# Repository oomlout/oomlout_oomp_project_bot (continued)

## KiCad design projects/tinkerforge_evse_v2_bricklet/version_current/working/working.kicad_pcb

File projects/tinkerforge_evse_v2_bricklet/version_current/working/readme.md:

# evse-v2-bricklet by Tinkerforge  
This is a harvested standardized copy of a project from github.  
The original project can be found at:  
https://github.com/Tinkerforge/evse-v2-bricklet  
Please consult that link for additional, details, files, and license information.  
Note: It was auto harvested and if the original repo had more than one board file or anything out of the ordinary the files here are likely not representative.

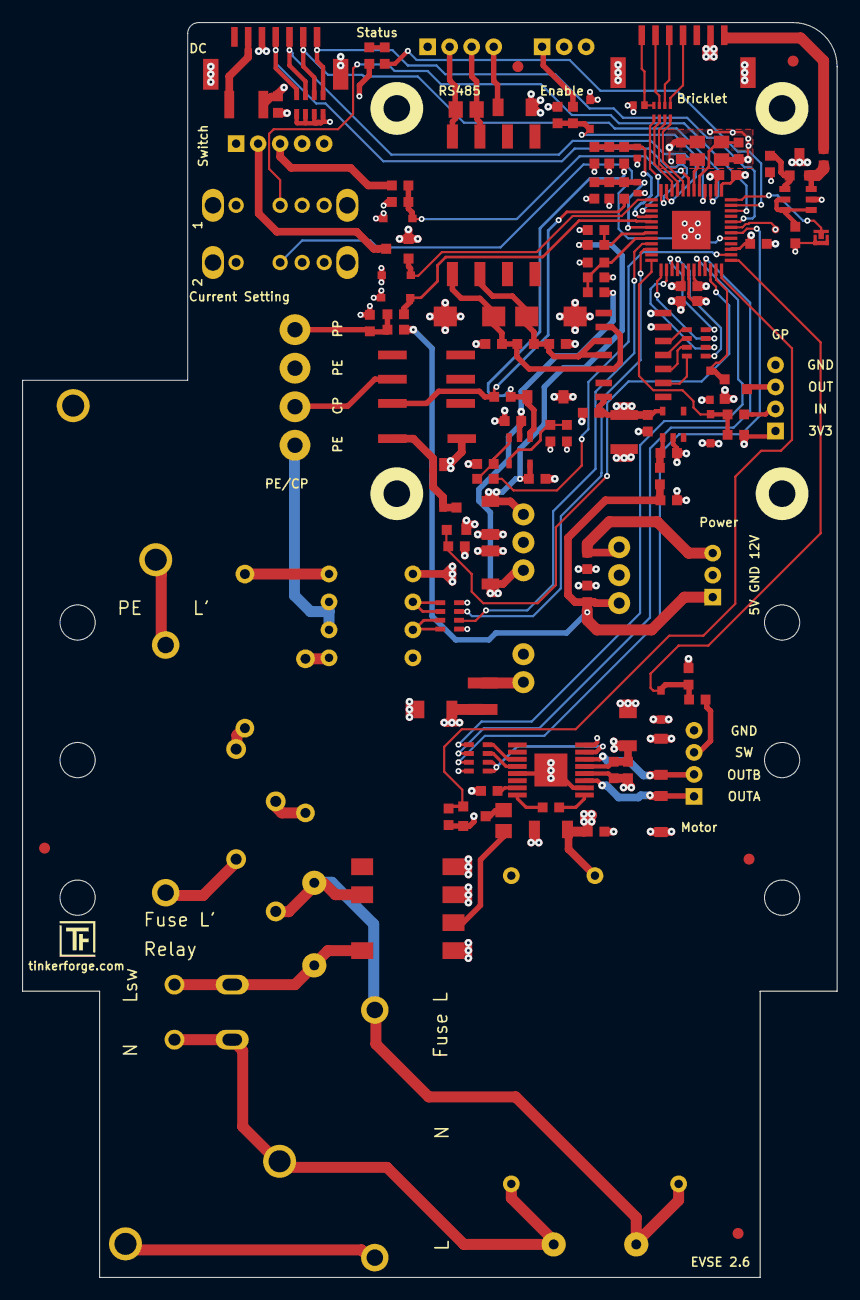
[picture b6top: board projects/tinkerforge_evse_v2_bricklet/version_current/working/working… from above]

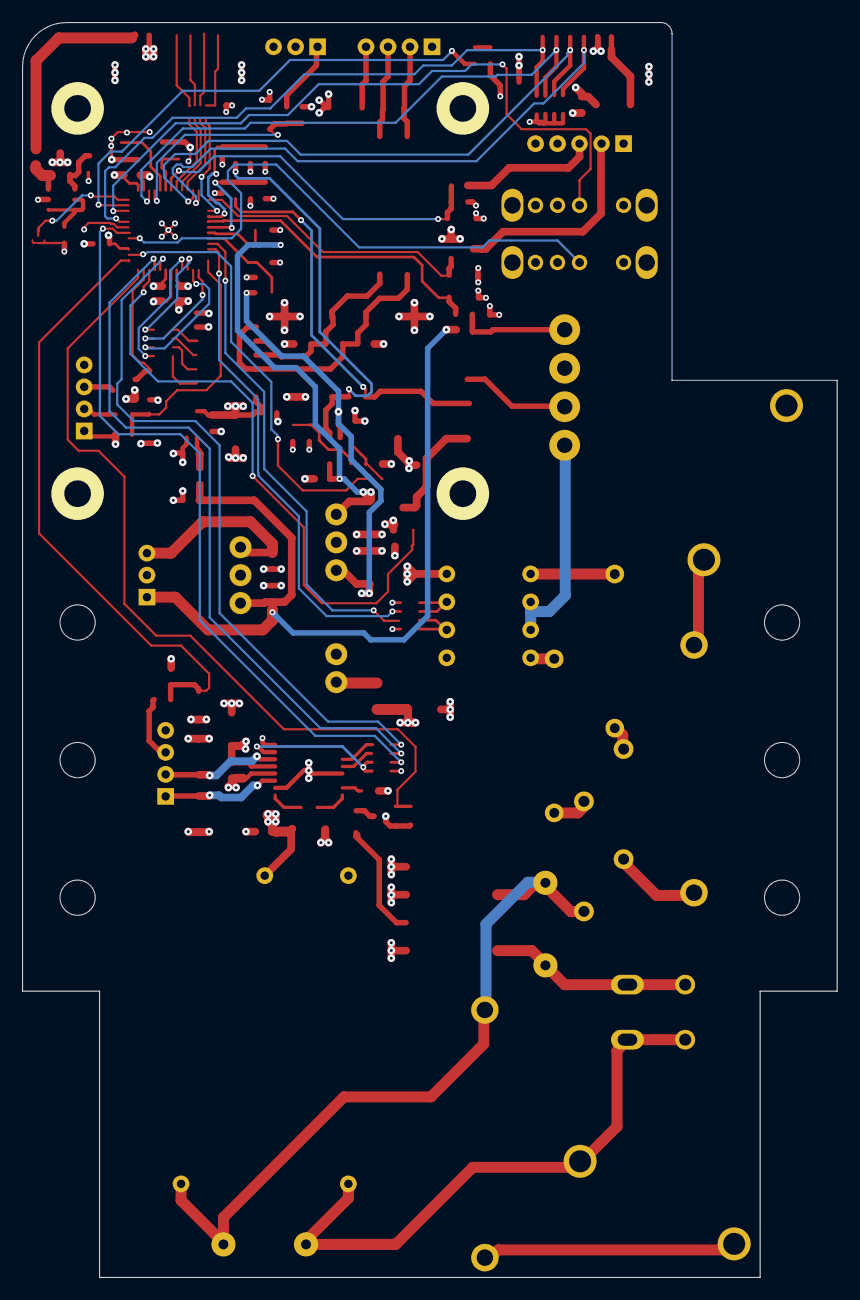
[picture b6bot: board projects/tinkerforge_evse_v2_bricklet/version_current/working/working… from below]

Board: 4 copper layers, 74.0 x 114.0 mm, 144 parts (2 on the bottom side), 100 nets.

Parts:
A101, A102, A103, A104: DRILL; DRILL_NP_35
A105, A106: Rail; din-rail-mount
C101: 220pF; C0402F
C102, C127, C130, C132: 100nF; C0603F
C103, C106, C107, C124, C125, C126: 1uF; C0603F
C104, C105, C108, C109: 4.7uF/50V; C1206
C110: 2.2uF; C0603F
C111: 100uF; C1210
C112, C113, C116, C117, C118, C119: 100nF/30V; C0603F
C114: 10uF; C1206
C120, C121: DNP; C0402F
C128, C129: 10pF; C0603F
C131: 220nF; C0603F
D101, D102, D104, D107, D110, D113, D114: ‎PESD3V3L1BA; SOD-323
D103: blue; D0603F
D105, D108, D109: SMF4L13CA; SOD-123FL
D106, D111: SMAJ24CA; DO-214AC
D112: B0520LW-7; SOD-123
D115, D116: 1N4007; DO-41
F101, F102: FUSE; Fuse-Holder-5x20
Fiducial_Mark: VAL**; Fiducial_Mark
Fiducial_Mark#2, Fiducial_Mark#3, Fiducial_Mark#4, Fiducial_Mark#5: VAL**; Fiducial_Mark
J101: Boot; SolderJumper
L101, L103: FB; R0603F
L102: NR3015T6R8M; NR3030
L104: WE-SL
P101: CON-SENSOR2; CON-SENSOR2_180
P102: Relay; LSF-SMT-500-02-135
P103, P104: L'+PE; wm_2491620000
P105: CP/PP/PE; OQ_4P_Vertical
P106: Power; JST-PH-3-THT
P107: Motor; JST-PH-4-THT
P108: Switch_LED; JST-PH-5-THT
P109: Enable; JST-PH-3-THT
P110: MODBUS; JST-PH-4-THT
P111: Debug; DEBUG_PAD
P112: DC-Protect; CON-SENSOR2_180
P113: GP; JST-PH-4-THT
PTC101: PTC 0.45A; C1206
Q101, Q103, Q104: 2N7002P; SOT23GDS
Q102: SI2305CDS-T1-GE3; SOT23GDS
Q105: SSM3J355R,LF; SOT23GDS
R1: 0; R1210
R101: 100; R0603F
R102, R110, R125: 75k; R0603F
R103, R112, R119, R121, R132, R139, R140: 10k; R0603F
R104, R108, R126, R129: 300k; R0603F
R105, R106, R109, R122, R127, R130: 100k; R0603F
R107: 910; R0603F
R111, R115, R117, R120, R123, R124, R131, R138: 1k; R0603F
R113, R128: MOV-10D391KTR; VAR_10mm
R114, R137: 120; R0805E
R116, R118: RNF12FTD249K; RNF12-2
R133: 47k; R0603F
R134, R136: 750; R0603F
R135: DNP; R0603F
R141: 2k; R0603F
REL101: AGQ200S12Z; AGQ2X0
RP101: 82; 4X0402
RP102: 10k; 0603X4
RP103, RP104: 1k; 4X0603
RP105: 10k; 4X0603
SW101, SW102: OS103011MS8QP1
U101: XMC1404; QFN48-EP2
U102: PEM1-S12-D12-S; PEM1S
U103: DMMT5401; SOT26
U105: OPA171AIDBV; SOT23-5
U106: A5950GLP; TSSOP16_EP
U108: AQH3213AX; AQ-H
U109: HCPL2731; DIP-8
U110: TPS70933DBVR; SOT23-5
U111: IRM02-12; IRM02
U112: WPMDL110
U113: SP3491; SOIC-14_3.9x8.7mm_Pitch1.27mm
X101: 16MHz; CRYSTAL_3225

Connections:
3V3: C102.1, C110.1, C111.1, C127.1, C130.1, C131.1, C132.2, D103.1 (A), P113.1, Q102.S, R102.2, R103.2, R105.2, R110.1, R115.2, R119.2, R121.2, R125.1, R132.2, R134.1, R139.2, RP103.5 (R4), RP103.6 (R3), RP103.7 (R2), RP103.8 (R1), RP104.1, RP105.1, RP105.4, SW101.4, SW102.4, U101.18 (VDD), U101.19 (VDDP), U101.27 (VDDP), U101.38 (VDDP), U106.8 (RESETn), U109.8 (VCC), U110.5 (OUT), U113.14 (VCC)
5V: C103.1, C107.1, C126.1, L101.2, P106.1, Q105.D, R1.1, R111.2, U103.5, U112.3 (VOUT)
485-D: RP102.4, U101.15 (P2.12/AIO)
485-DE: RP102.3, U101.13 (P2.10/AIO)
485-R: RP102.1, U101.16 (P2.13/AIO)
485-~REB: RP102.2, U101.14 (P2.11/AIO)
+12V: C109.1, C113.2, R129.2, U102.7 (+Vo), U105.5 (V+)
-12V: C108.2, C112.2, R104.2, U102.5 (-Vo), U105.2 (V-)
AC1: RP105.3, U101.9 (P2.6_AI)
AC2: RP105.2, U101.10 (P2.7_AI)
BOOT: J101.2, U101.36 (P0.7_IO)
CP-DISCONNECT: Q103.G, R138.2, U101.22 (P1.4_IHO)
CP-PWM: R101.2, U101.26 (P1.0_IHO)
CPOUT: R107.2, R108.2, REL101.7
CPOUT2: P105.2, REL101.6
DC-ERR: P112.1, RP103.4, U101.32 (P0.3_IO)
DC-TST: P112.2, RP103.3, U101.39 (P0.8_IO/RTC_XTAL1)
DC-X6: P112.3, RP103.2, U101.47 (P4.4_IO)
DC-X30: P112.4, RP103.1, U101.48 (P4.5_IO)
ENABLE: D102.1 (A), R131.1, R132.1, U101.40 (P0.9_IO/RTC_XTAL2)
GND: C101.2, C102.2, C103.2, C104.2, C105.2, C106.2, C107.2, C108.1, C109.2, C110.2, C111.2, C112.1, C113.1, C114.2, C118.1, C119.1, C120.2, C121.2, C124.2, C125.2, C126.2, C127.2, C128.2, C129.2, C130.2, C131.2, C132.1, D101.2 (K), D102.2 (K), D104.1 (A), D105.2 (K), D106.2 (K), D107.1 (A), D108.2 (K), D109.2 (K), D110.2 (K), D111.2 (K), D113.2 (K), D114.2 (K), J101.1, P101.2, P101.EP, P104.2 (PM), P105.1, P105.3, P106.2, P107.4, P108.4, P108.5, P109.2 (PM), P109.3, P112.5, P112.EP, P113.4, PTC101.2, Q101.S, Q103.S, Q104.S, R106.1, R109.2, R122.2, R127.2, R130.2, R133.1, R136.2, R138.1, R140.1, R141.1, SW101.1, SW102.1, U101.17 (VSS), U101.37 (VSSP), U101.EP (VSSP), U102.2 (GND), U102.6 (0V), U106.2 (GND), U106.4 (LSS), U106.13 (MODE), U106.EP (PAD), U108.1, U108.3, U108.4, U109.2 (-1), U109.3 (-2), U109.5 (GND), U110.2 (GND), U111.4 (V-), U112.2 (GND), U113.6 (GND), U113.7 (GND), X101.3
GP-IN: D113.1 (A), R123.1, R139.1, U101.12 (P2.9_AI)
GP-OUT: D114.1 (A), Q104.G, U101.23 (P1.3_IHO)
INPUT-MOTOR-SWITCH: D104.2 (K), R117.1, R119.1, U101.25 (P1.1_IHO)
L: D116.1 (A), F101.2, R113.2, R128.1, U108.6, U111.1 (L)
LED: D101.1 (A), Q101.G, U101.1 (P4.6_IO)
MOTOR_ENABLE: RP104.3, U101.21 (P1.5_IHO)
MOTOR_PHASE: RP104.4, U101.20 (P1.6_IHO)
N: P102.2 (PM), P103.1, R128.2, U111.2 (N)
unnamed: C101.1, P101.7, RP101.4
unnamed: C106.1, L101.1, U110.1 (IN)
unnamed: C116.1, U106.16 (CP2)
unnamed: C116.2, U106.1 (CP1)
unnamed: C117.2, U106.15 (VCP)
unnamed: C128.1, U101.41 (P0.10_IO/XTAL1), X101.2
unnamed: C129.1, U101.42 (P0.11_IO/XTAL2), X101.1
unnamed: D103.2 (K), R124.2
unnamed: D105.1 (A), R107.1, R126.2, U105.1 (OUT)
unnamed: D106.1 (A), L104.2, R135.2, R136.1, U113.10 (Z), U113.11 (B)
unnamed: D108.1 (A), P107.1, U106.3 (OUTA)
unnamed: D109.1 (A), P107.2, U106.6 (OUTB)
unnamed: D111.1 (A), L104.1, R134.2, R135.1, U113.9 (Y), U113.12 (A)
unnamed: D112.1 (A), Q103.D, REL101.8
unnamed: D115.1 (A), F102.2
unnamed: D115.2 (K), R118.1
unnamed: D116.2 (K), R116.1
unnamed: F101.1, P103.2 (PM)
unnamed: F102.1, P104.1
unnamed: L102.2, U102.1 (VIN)
unnamed: L103.1, Q105.S, U103.6
unnamed: L103.2, P101.1
unnamed: L104.7, P110.3, R137.1
unnamed: L104.8, P110.2, R137.2
unnamed: P101.4, RP101.1
unnamed: P101.5, RP101.2
unnamed: P101.6, RP101.3
unnamed: P102.1, R113.1, U108.8
unnamed: P105.4, R111.1, R112.1, R141.2
unnamed: P107.3, R117.2
unnamed: P108.2, Q101.D
unnamed: P108.3, R120.2
unnamed: P109.1, R131.2
unnamed: P110.4, PTC101.1
unnamed: P111.1, U101.31 (P0.2_IO)
unnamed: P112.6, R1.2
unnamed: P113.2, R123.2
unnamed: P113.3, Q104.D
unnamed: Q102.D, R114.1
unnamed: Q105.G, R133.2, U103.1
unnamed: R101.1, R103.1, U105.3 (IN+)
unnamed: R105.1, R106.2, U105.4 (IN-)
unnamed: R114.2, U108.2
unnamed: R116.2, U109.4 (+2)
unnamed: R118.2, U109.1 (+1)
unnamed: R124.1, U101.35 (P0.6_IO)
unnamed: R140.2, U103.2, U103.3, U103.4
unnamed: RP102.5 (R4), U113.5 (D)
unnamed: RP102.6 (R3), U113.4 (DE)
unnamed: RP102.7 (R2), U113.3 (~REB)
unnamed: RP102.8 (R1), U113.2 (R)
unnamed: RP104.5 (R4), U106.11 (PHASE)
unnamed: RP104.6 (R3), U106.12 (ENABLE)
unnamed: RP104.7 (R2), RP104.8 (R1), U106.7 (FAULTn)
unnamed: RP105.5 (R4), RP105.6 (R3), U109.6 (VO2)
unnamed: RP105.7 (R2), RP105.8 (R1), U109.7 (VO1)
P0_0: SW101.2, U101.29 (P0.0_IO)
P0_5: SW102.2, U101.34 (P0.5_IO)
RELAY: Q102.G, R115.1, U101.24 (P1.2_IHO)
S-CLK: RP101.7 (R2), U101.45 (P0.14_IO)
S-CS: RP101.8 (R1), U101.44 (P0.13_IO)
S-MISO: RP101.5 (R4), U101.3 (P2.0_AIO)
S-MOSI: RP101.6 (R3), U101.46 (P0.15_IO)
SWITCH: D110.1 (A), R120.1, R121.1, U101.43 (P0.12_IO)
V12: R129.1, R130.1, U101.7 (P2.4_AI)
V-12: R102.1, R104.1, R122.1, U101.8 (P2.5_AI)
VCC: C104.1, C105.1, C114.1, C117.1, C118.2, C119.2, C124.1, C125.1, D112.2 (K), L102.1, P106.3, P108.1, P110.1, REL101.1, U106.5 (VBB), U111.3 (V+), U112.1 (VIN)
VCP1: C120.1, R125.2, R126.1, R127.1, U101.4 (P2.1_AIO)
VCP2: C121.1, R108.1, R109.1, R110.2, U101.6 (P2.3_AI)
VPP: D107.2 (K), R112.2, U101.5 (P2.2_AI)
~MOTOR_FAULT: RP104.2, U101.30 (P0.1_IO)

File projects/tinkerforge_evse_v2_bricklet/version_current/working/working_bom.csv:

Row,Description,Part,References,Value,Footprint,Quantity Per PCB,Status,Datasheet
1,,DRILL,A101 A102 A103 A104,DRILL,DRILL_NP_35,4, ,
2,,DRILL,A105 A106,Rail,din-rail-mount,2, ,
3,,C,C128 C129,10pF,C0603F,2, ,
4,,C,C101,220pF,C0402F,1, ,
5,,C,C102 C127 C130,100nF,C0603F,3, ,
6,,C,C132,100nF,C0603F,1, ,
7,,C,C131,220nF,C0603F,1, ,
8,,C,C103 C106 C107 C124 C125 C126,1uF,C0603F,6, ,
9,,C,C110,2.2uF,C0603F,1, ,
10,,C,C114,10uF,C1206,1, ,
11,,C,C111,100uF,C1210,1, ,
12,,C,C112 C113 C116 C117 C118 C119,100nF/30V,C0603F,6, ,
13,,C,C104 C105 C108 C109,4.7uF/50V,C1206,4, ,
14,,DIODE,D115 D116,1N4007,DO-41,2, ,
15,,DIODESCH,D112,B0520LW-7,SOD-123,1, ,
16,,TVS,D106 D111,SMAJ24CA,DO-214AC,2, ,
17,,TVS,D105 D108 D109,SMF4L13CA,SOD-123FL,3, ,
18,,LED,D103,blue,D0603F,1, ,
19,,TVS,D101 D102 D104 D107 D110 D113 D114,‎PESD3V3L1BA,SOD-323,7, ,
20,,FUSE,F101 F102,FUSE,Fuse-Holder-5x20,2, ,
21,Connector 01x02,CONN_01X02,J101,Boot,SolderJumper,1, ,
22,,INDUCTs,L101 L103,FB,R0603F,2, ,
23,,INDUCTOR,L102,NR3015T6R8M,NR3030,1, ,
24,,WE-SL,L104,WE-SL,WE-SL,1, ,
25,,CON-SENSOR2,P101,CON-SENSOR2,CON-SENSOR2_180,1, ,
26,,CONN_4,P105,CP/PP/PE,OQ_4P_Vertical,1, ,
27,,CON-SENSOR2-BLANK,P112,DC-Protect,CON-SENSOR2_180,1, ,
28,,CONN_1,P111,Debug,DEBUG_PAD,1, ,
29,,CONN_3,P109,Enable,JST-PH-3-THT,1, ,
30,,CONN_4,P113,GP,JST-PH-4-THT,1, ,
31,,CONN_2,P103 P104,L'+PE,wm_2491620000,2, ,
32,Connector 01x04,CONN_01X04,P110,MODBUS,JST-PH-4-THT,1, ,
33,,CONN_4,P107,Motor,JST-PH-4-THT,1, ,
34,Connector 01x03,CONN_01X03,P106,Power,JST-PH-3-THT,1, ,
35,,CONN_2,P102,Relay,LSF-SMT-500-02-135,1, ,
36,,CONN_5,P108,Switch_LED,JST-PH-5-THT,1, ,
37,,PTC,PTC101,PTC 0.45A,C1206,1, ,
38,"Transistor P-MOSFET, collector connected to mounting plane (general)",MOSFET_N_CH,Q101 Q103 Q104,2N7002P,SOT23GDS,3, ,
39,Transistor P-MOSFET (general),MOSFET_P_CH,Q102,SI2305CDS-T1-GE3,SOT23GDS,1, ,
40,Transistor P-MOSFET (general),MOSFET_P_CH,Q105,"SSM3J355R,LF",SOT23GDS,1, ,
41,,R,R1,0,R1210,1, ,
42,,R,R101,100,R0603F,1, ,
43,,R,R114,120,R0805E,1, ,
44,,R,R137,120,R0805E,1, ,
45,,R,R134 R136,750,R0603F,2, ,
46,,R,R107,910,R0603F,1, ,
47,,R,R111 R115 R117 R120 R123 R124 R131 R138,1k,R0603F,8, ,
48,,R,R141,2k,R0603F,1, ,
49,,R,R103 R112 R119 R121 R132 R139 R140,10k,R0603F,7, ,
50,,R,R133,47k,R0603F,1, ,
51,,R,R102 R110 R125,75k,R0603F,3, ,
52,,R,R105 R106 R109 R122 R127 R130,100k,R0603F,6, ,
53,,R,R104 R108 R126 R129,300k,R0603F,4, ,
54,,Varistor,R113 R128,MOV-10D391KTR,VAR_10mm,2, ,
55,,R,R116 R118,RNF12FTD249K,RNF12-2,2, ,
56,,AGQ2X0,REL101,AGQ200S12Z,AGQ2X0,1, ,
57,4 resistors Pack,R_PACK4,RP102,10k,0603X4,1, ,
58,4 resistors Pack,R_PACK4,RP105,10k,4X0603,1, ,
59,4 resistors Pack,R_PACK4,RP103 RP104,1k,4X0603,2, ,
60,4 resistors Pack,R_PACK4,RP101,82,4X0402,1, ,
61,,OS103011MS8QP1,SW101 SW102,OS103011MS8QP1,OS103011MS8QP1,2, ,
62,,A5950GLP,U106,A5950GLP,TSSOP16_EP,1, ,
63,,AQ-H,U108,AQH3213AX,AQ-H,1, ,
64,,DMMT5401,U103,DMMT5401,SOT26,1, ,
65,,HCPL-2731-000E,U109,HCPL2731,DIP-8,1, ,
66,,IRM,U111,IRM02-12,IRM02,1, ,
67,,OPA344,U105,OPA171AIDBV,SOT23-5,1, ,
68,,PEM1-S12-D12-S,U102,PEM1-S12-D12-S,PEM1S,1, ,
69,,SP3491,U113,SP3491,SOIC-14_3.9x8.7mm_Pitch1.27mm,1, ,
70,,TPS709,U110,TPS70933DBVR,SOT23-5,1, ,
71,,WPMDL110,U112,WPMDL110,WPMDL110,1, ,
72,,XMC1XXX48,U101,XMC1404,QFN48-EP2,1, ,
73,,CRYSTAL_3225,X101,16MHz,CRYSTAL_3225,1, ,





Project info:
Schematic:,working
Variant:,default
Revision:,2.0.6
Date:,2023-01-20
KiCad Version:,7.0.6-7.0.6~ubuntu22.04.1
Statistics:
Component Groups:,75
Component Count:,139 (79 SMD/ 60 THT)
Fitted Components:,136 (78 SMD/ 58 THT)
Number of PCBs:,1
Total Components:,136

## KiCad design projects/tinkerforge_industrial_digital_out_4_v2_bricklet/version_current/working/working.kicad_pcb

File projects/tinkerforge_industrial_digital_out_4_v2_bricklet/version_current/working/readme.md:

# OOMP Project  
## industrial-digital-out-4-v2-bricklet  by Tinkerforge  
  
oomp key: oomp_projects_flat_tinkerforge_industrial_digital_out_4_v2_bricklet  
(snippet of original readme)  

  full source readme at [readme_src.md](readme_src.md)  
  
source repo at: [https://github.com/Tinkerforge/industrial-digital-out-4-v2-bricklet](https://github.com/Tinkerforge/industrial-digital-out-4-v2-bricklet)  
## Board  

## Schematic  

[schematic pdf](working_schematic.pdf)  
## Images

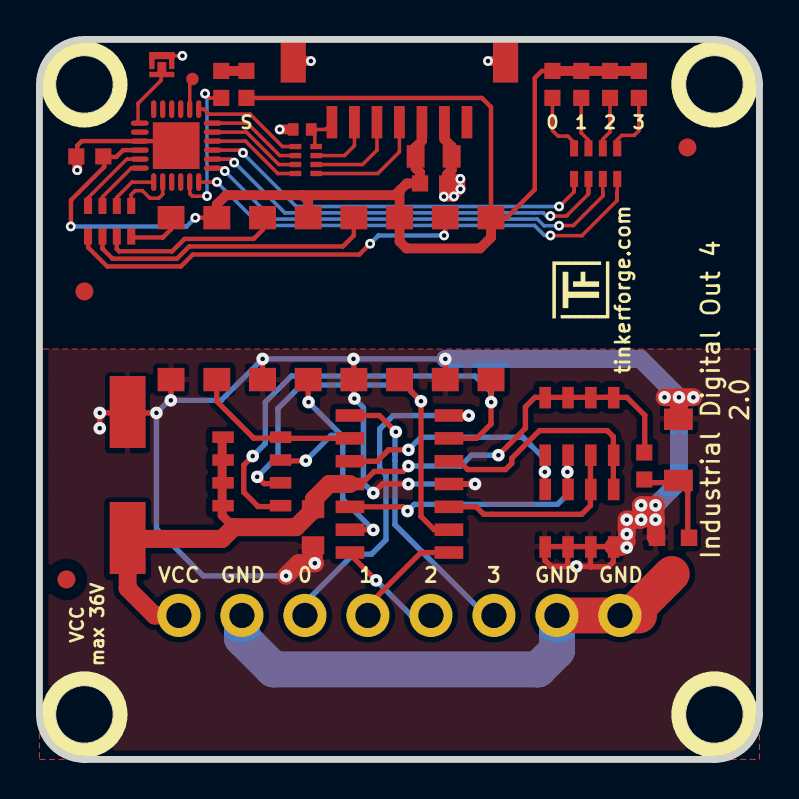
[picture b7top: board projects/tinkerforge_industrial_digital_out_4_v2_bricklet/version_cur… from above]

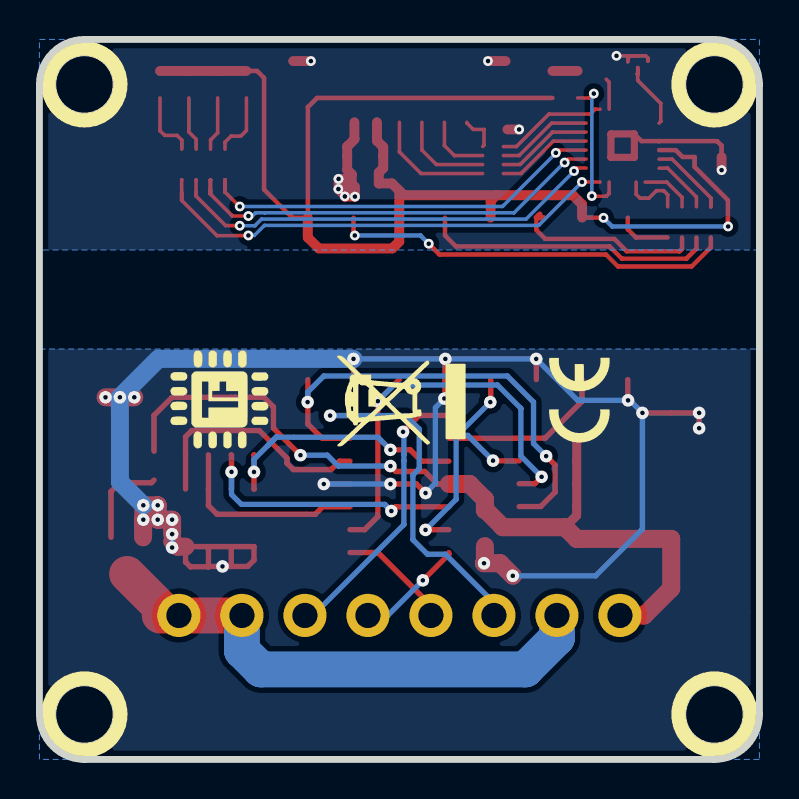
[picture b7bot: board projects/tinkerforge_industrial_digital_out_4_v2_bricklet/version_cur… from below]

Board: 2 copper layers, 40.0 x 40.0 mm, 37 parts (2 on the bottom side), 46 nets.

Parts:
C1: 10uF; C0805
C2: 100nF; C0805
C3: 68µF/50V; ELKO_83
C4: 220pF; C0402F
C5: 1uF; C0603F
C6: 100nF; C0603F
D1: Z12V; MiniMelf
D2, D3, D4, D5, D6: blue; D0603F
Fiducial_Mark: VAL**; Fiducial_Mark
Fiducial_Mark#2, Fiducial_Mark#3: VAL**; Fiducial_Mark
P1: CON-SENSOR2
P2: Digital Output; OQ_8P
P3: DEBUG; DEBUG_PAD
P4: BOOT; SolderJumper
Q1: FDN5630; SOT23GDS
R1: 100k; R0603F
R2: 1k; R0603F
RP1, RP6: 1k; 0603X4
RP2: 12k; 1206X4
RP3, RP4: 10k; 1206X4
RP5: 82; 4X0402
U1: XMC1100; QFN24-4x4mm-0.5mm
U2: LTV846S; OPTO-SMD16
U3: OPA4171AIDR; SOP14
U4, U5, U6, U7: DRILL; DRILL_NP
VAL: WEEE_7mm
VAL#2: CE_5mm

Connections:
3V3: C1.1, C5.1, C6.1, D2.1, D3.1, D4.1, D5.1, D6.1, P1.3, U1.10, U2.1, U2.3, U2.5, U2.7
AGND: C2.2, C3.2, D1.1, Q1.S, RP4.1, RP4.2, RP4.3, RP4.4, U2.9, U2.11, U2.13, U2.15, U3.11
GND: C1.2, C4.2, C5.2, C6.2, P1.2, P1.EP, P4.1, U1.9, U1.EXP
unnamed: C4.1, P1.7, RP5.4
unnamed: D1.2, Q1.G, R1.2
unnamed: D2.2, R2.2
unnamed: D3.2, RP6.8
unnamed: D4.2, RP6.7
unnamed: D5.2, RP6.6
unnamed: D6.2, RP6.5
unnamed: P1.4, RP5.1
unnamed: P1.5, RP5.2
unnamed: P1.6, RP5.3
unnamed: P2.2, P2.7, P2.8, Q1.D
unnamed: P2.3, U3.14
unnamed: P2.4, U3.8
unnamed: P2.5, U3.7
unnamed: P2.6, U3.1
unnamed: P3.1, U1.2
unnamed: P4.2, U1.7
unnamed: R2.1, U1.17
unnamed: RP1.1, U2.2
unnamed: RP1.2, U2.4
unnamed: RP1.3, U2.6
unnamed: RP1.4, U2.8
unnamed: RP2.1, U2.16, U3.13
unnamed: RP2.2, U2.14, U3.9
unnamed: RP2.3, U2.12, U3.6
unnamed: RP2.4, U2.10, U3.2
unnamed: RP3.1, RP4.8, U3.3
unnamed: RP3.2, RP4.7, U3.5
unnamed: RP3.3, RP4.6, U3.10
unnamed: RP3.4, RP4.5, U3.12
unnamed: RP6.1, U1.21
unnamed: RP6.2, U1.20
unnamed: RP6.3, U1.19
unnamed: RP6.4, U1.18
OUTPUT1: RP1.5, U1.14
OUTPUT2: RP1.6, U1.13
OUTPUT3: RP1.7, U1.12
OUTPUT4: RP1.8, U1.11
S-CLK: RP5.7, U1.23
S-CS: RP5.8, U1.22
S-MISO: RP5.5, U1.1
S-MOSI: RP5.6, U1.24
VPP: C2.1, C3.1, P2.1, R1.1, RP2.5, RP2.6, RP2.7, RP2.8, RP3.5, RP3.6, RP3.7, RP3.8, U3.4

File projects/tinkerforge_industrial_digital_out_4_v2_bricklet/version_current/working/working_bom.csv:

"Id";"Designator";"Footprint";"Quantity";"Designation";"Supplier and ref";
1;"Fiducial_Mark,Fiducial_Mark,Fiducial_Mark";"Fiducial_Mark";3;"VAL**";;;
2;"G***";"Logo_31x31";1;"Logo_31x31";;;
3;"P3";"DEBUG_PAD";1;"DEBUG";;;
4;"U1";"QFN24-4x4mm-0.5mm";1;"XMC1100";;;
5;"C1";"C0805";1;"10uF";;;
6;"C2";"C0805";1;"100nF";;;
7;"C3";"ELKO_83";1;"68µF/50V";;;
8;"C4";"C0402F";1;"220pF";;;
9;"C5";"C0603F";1;"1uF";;;
10;"C6";"C0603F";1;"100nF";;;
11;"D1";"MiniMelf";1;"Z12V";;;
12;"D2,D3,D4,D5,D6";"D0603F";5;"blue";;;
13;"P1";"CON-SENSOR2";1;"CON-SENSOR2";;;
14;"P2";"OQ_8P";1;"Digital Output";;;
15;"P4";"SolderJumper";1;"BOOT";;;
16;"Q1";"SOT23GDS";1;"FDN5630";;;
17;"R1";"R0603F";1;"100k";;;
18;"R2";"R0603F";1;"1k";;;
19;"RP1,RP6";"0603X4";2;"1k";;;
20;"RP2";"1206X4";1;"12k";;;
21;"RP3,RP4";"1206X4";2;"10k";;;
22;"RP5";"4X0402";1;"82";;;
23;"U2";"OPTO-SMD16";1;"LTV846S";;;
24;"U3";"SOP14";1;"OPA4171AIDR";;;
25;"U4,U5,U6,U7";"DRILL_NP";4;"DRILL";;;
26;"VAL";"WEEE_7mm";1;"WEEE_7mm";;;
27;"VAL";"CE_5mm";1;"CE_5mm";;;
28;"G***";"Logo_CoMCU";1;"LOGO";;;
